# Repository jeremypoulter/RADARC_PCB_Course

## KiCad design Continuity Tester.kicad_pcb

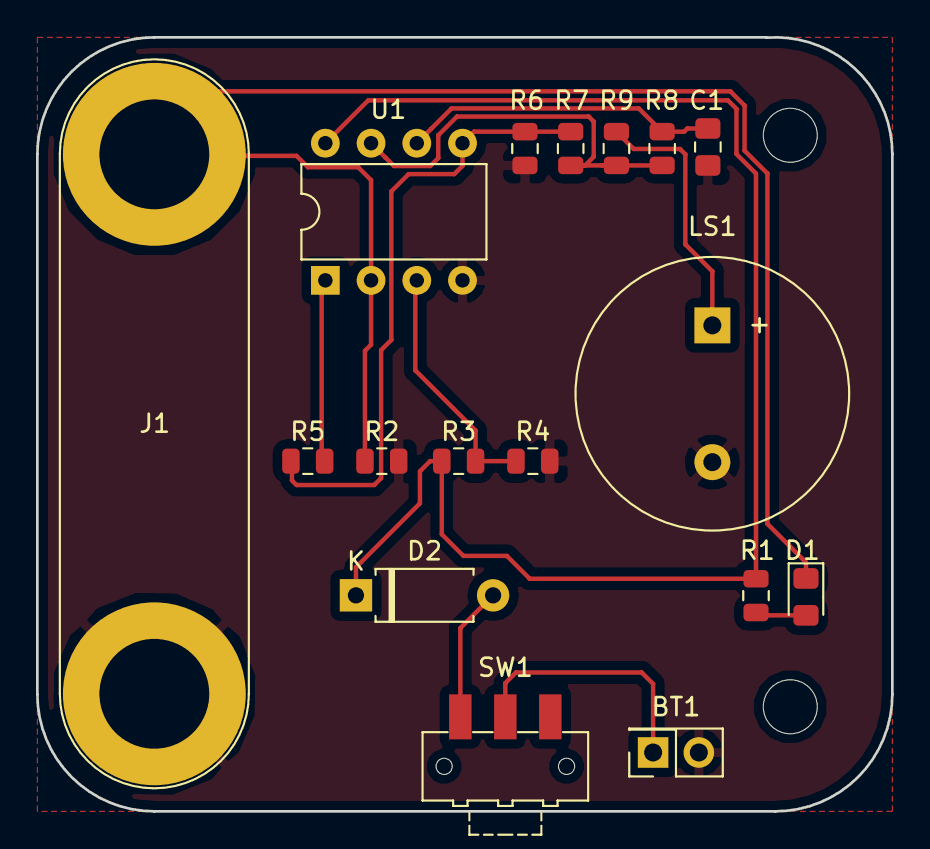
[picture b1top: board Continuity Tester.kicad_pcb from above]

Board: 2 copper layers, 47.5 x 43.0 mm, 19 parts (0 on the bottom side), 12 nets.

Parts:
BT1: Battery; PinSocket_2x01_P2.54mm_Vertical
C1: 15n; C_0805_2012Metric_Pad1.15x1.40mm_HandSolder
D1: LED; LED_0805_2012Metric_Pad1.15x1.40mm_HandSolder
D2: IN4148; D_A-405_P7.62mm_Horizontal
J1: Test Probes; Banana_Jack_2Pin
LS1: KU57M; Buzzer_15x7.5RM7.6
MH1, MH2: MountingHole; MountingHole_3mm
R1: 6K8; R_0805_2012Metric
R2: 47; R_0805_2012Metric
R3: 150K; R_0805_2012Metric
R4: 270; R_0805_2012Metric
R5, R6: 10K; R_0805_2012Metric
R7, R8: 100K; R_0805_2012Metric
R9: 4K7; R_0805_2012Metric
SW1: SW_SPST; SW_SPDT_CK-JS102011SAQN
U1: CA3240; DIP-8_W7.62mm

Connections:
+9V: BT1.1, SW1.2
GND: BT1.2, C1.2, J1.1, LS1.2, R2.2, R4.2, R6.2, U1.4
unnamed: C1.1, R8.2, U1.6
unnamed: D1.1, J1.2, R2.1, U1.2
unnamed: D1.2, R1.2
unnamed: D2.2, SW1.1
unnamed: LS1.1, R9.2
unnamed: R3.2, R4.1, U1.3
unnamed: R5.1, R6.1, R7.2, U1.5
unnamed: R5.2, U1.1
unnamed: R7.1, R8.1, R9.1, U1.7
VCC: D2.1, R1.1, R3.1, U1.8

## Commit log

2018-11-02 Files from PCB course
2018-11-02 Added in the mounting holes
